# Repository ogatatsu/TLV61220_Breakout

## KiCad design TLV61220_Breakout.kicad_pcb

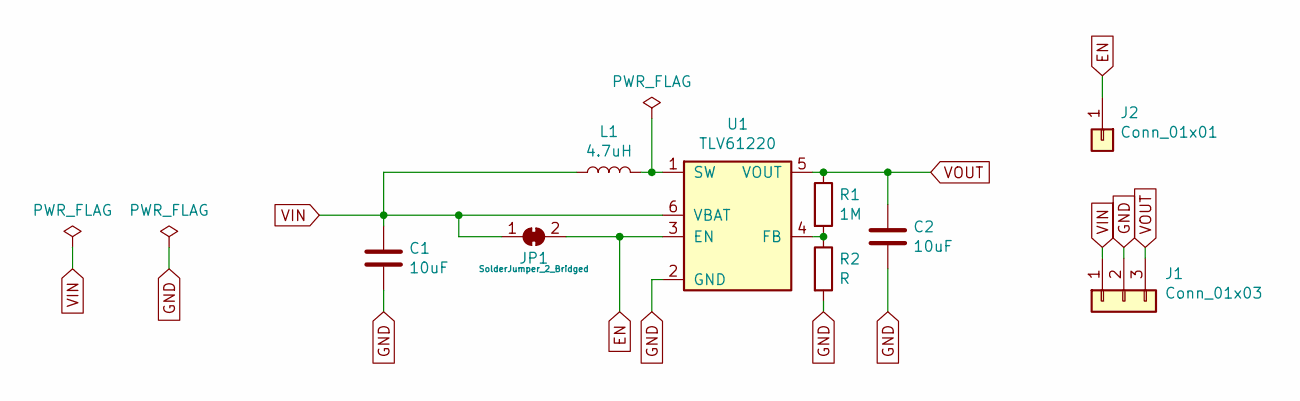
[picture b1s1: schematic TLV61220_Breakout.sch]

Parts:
C1, C2: 10uF; C_0603_1608Metric_Pad1.05x0.95mm_HandSolder
J1: Conn_01x03; Connector_2.54mm_03
J2: Conn_01x01; Connector_2.54mm_01
JP1: SolderJumper_2_Bridged; SolderJumper-2_P1.3mm_Bridged_RoundedPad1.0x1.5mm
L1: 4.7uH; L_1210_3225Metric
R1: 1M; R_0603_1608Metric_Pad1.05x0.95mm_HandSolder
R2: R; R_0603_1608Metric_Pad1.05x0.95mm_HandSolder
U1: TLV61220; SOT-23-6_Handsoldering

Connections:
EN: J2.1, JP1.2 (B), U1.3 (EN)
GND: C1.2, C2.2, J1.2, R2.2, U1.2 (GND)
unnamed: L1.2, U1.1 (SW)
unnamed: R1.2, R2.1, U1.4 (FB)
VIN: C1.1, J1.1, JP1.1 (A), L1.1, U1.6 (VBAT)
VOUT: C2.1, J1.3, R1.1, U1.5 (VOUT)

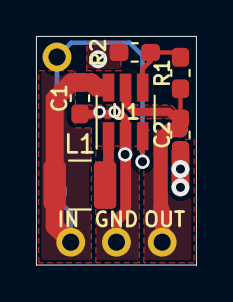
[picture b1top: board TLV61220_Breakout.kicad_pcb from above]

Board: 2 copper layers, 8.9 x 12.7 mm, 9 parts (1 on the bottom side), 6 nets.

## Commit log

2020-11-08 add schematic
